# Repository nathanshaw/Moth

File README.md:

# Speculator
This repo holds all the code, schematics, and PCB layouts for all series of the Speculator bot.

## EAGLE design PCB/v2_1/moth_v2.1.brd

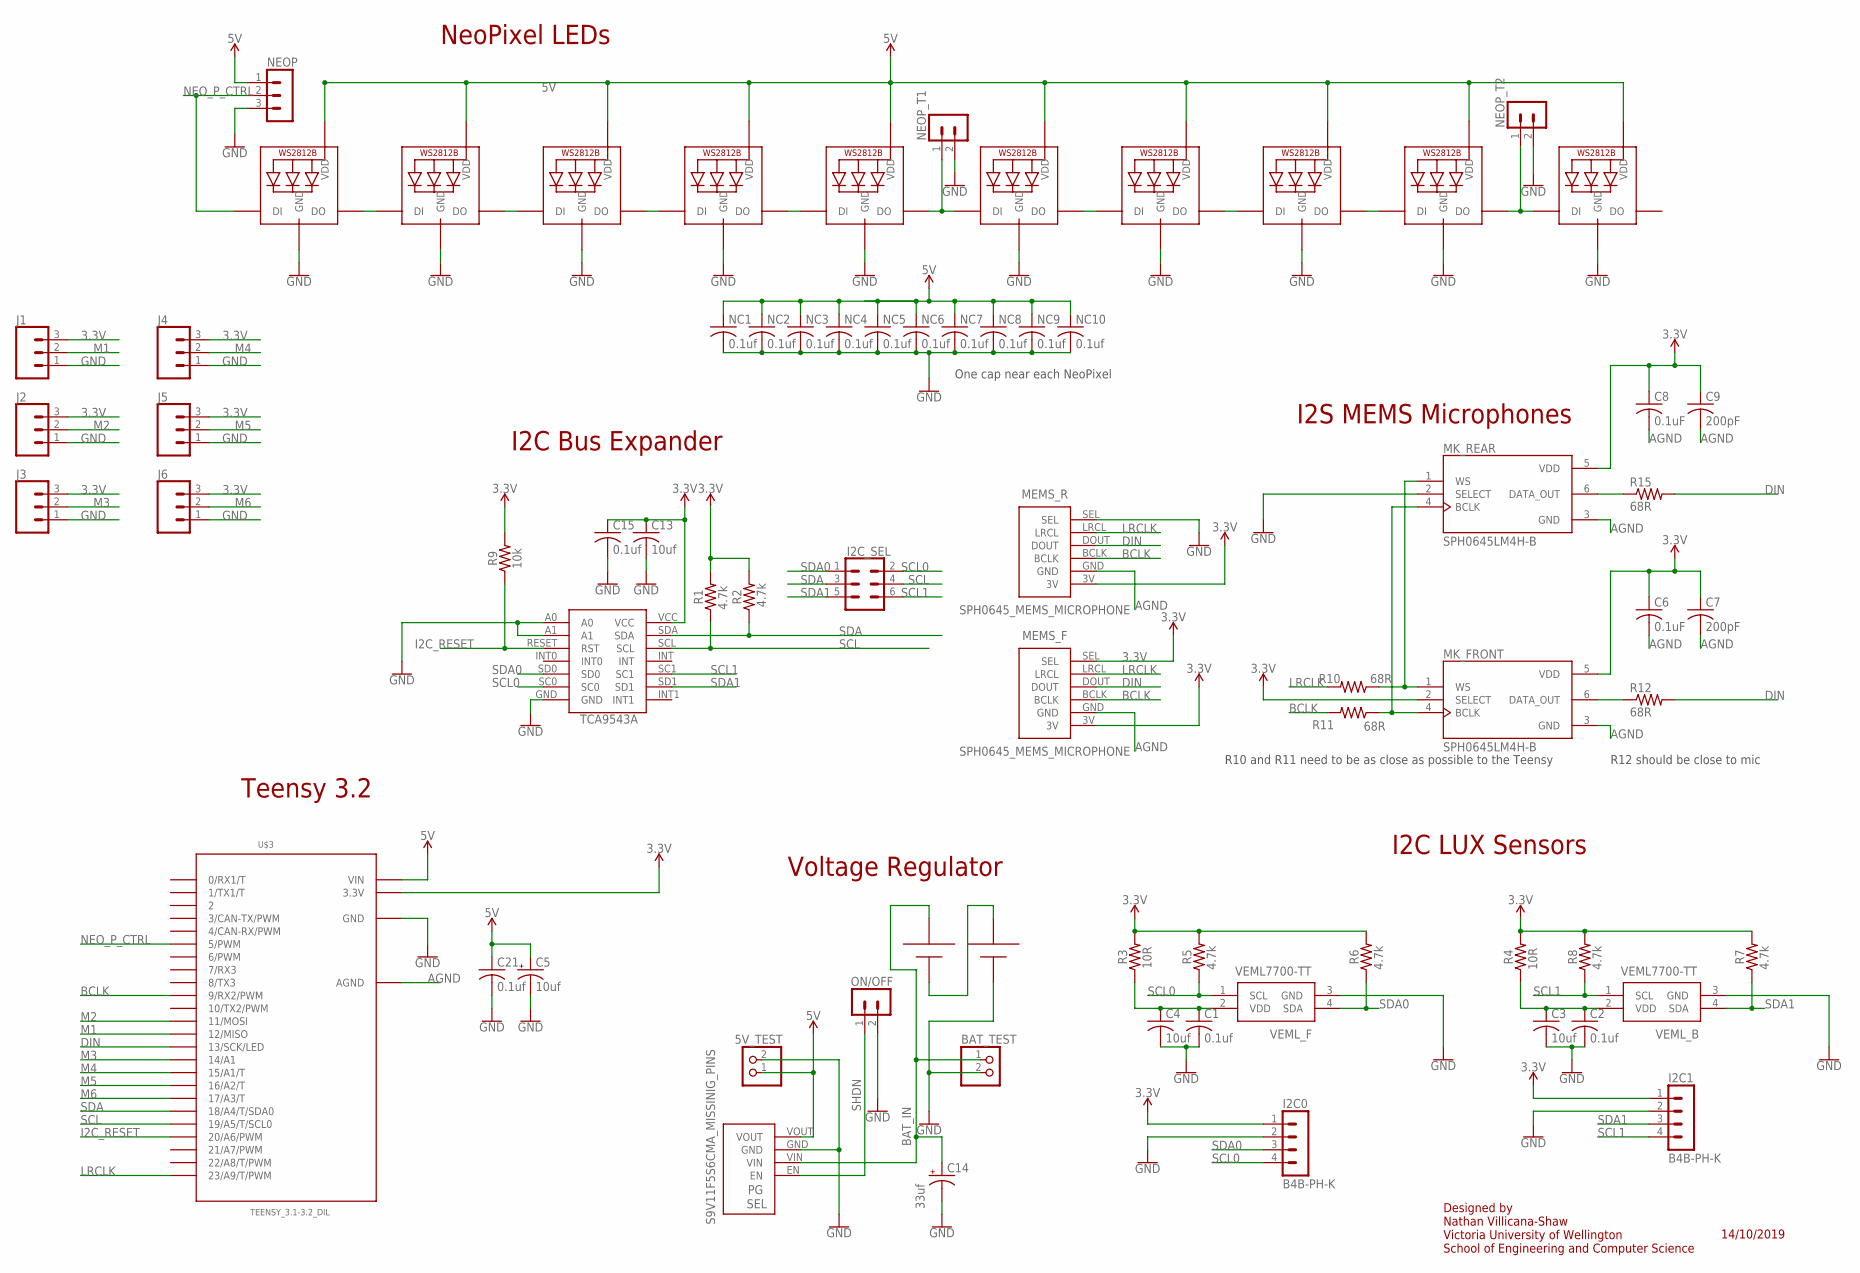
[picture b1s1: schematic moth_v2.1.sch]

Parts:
5V_TEST: PINHD-1X2; 1X02
BAT_TEST: PINHD-1X2; 1X02
C1, C2, C15, C21: 0.1uf; C1206K
C3, C4, C13: 10uf; C1206K
C5: 10uf; E2,5-6
C6, C8: 0.1uF; C1206K
C7, C9: 200pF; C1206K
C14: 33uf; E2-5
I2C0, I2C1: B4B-PH-K
I2C_SEL: FEMALE 2x3; 2X3
J1, J2, J3, J4, J5, J6: CONN_03; 1X03
MEMS_F: SPH0645_MEMS_MICROPHONE; SPH0645
MEMS_R: SPH0645_MEMS_MICROPHONE; SPH0645
MK_FRONT: SPH0645LM4H-B; MIC_SPH0645LM4H-B
MK_REAR: SPH0645LM4H-B; MIC_SPH0645LM4H-B
NC1, NC2, NC3, NC4, NC5, NC6, NC7, NC8, NC9, NC10: 0.1uf; C1206K
NEO1, NEO2, NEO3, NEO4, NEO5, NEO6, NEO7, NEO8, NEO9, NEO10: WS2812B5050; WS2812B
NEOP: B3B-PH-K
NEOP_T1, NEOP_T2: B2B-PH-K
ON/OFF: B2B-PH-K
R1, R2, R5, R6, R7, R8: 4.7k; R1206W
R3, R4: 10R; R1206W
R9: 10k; R1206W
R10, R11, R12, R15: 68R; M1206
U$1: TCA9543A; SO14
U$2: BK-18650-PC4; 18650-PC4
U$3: TEENSY_3.1-3.2_DIL; TEENSY_3.0-3.2&LC_DIL
U$6: S9V11F5S6CMA_MISSINIG_PINS; S9V11F3S5CMA_MISSING_PINS
VEML_B: VEML7700-TT; VEML7700
VEML_F: VEML7700-TT; VEML7700

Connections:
3.3V: C6.1, C7.1, C8.1, C9.1, C13.1, C15.1, I2C0.1, I2C1.1, J1.3, J2.3, J3.3, J4.3, J5.3, J6.3, MEMS_F.3V, MEMS_F.SEL, MEMS_R.3V, MK_FRONT.2 (SELECT), MK_FRONT.5 (VDD), MK_REAR.5 (VDD), R1.2, R2.2, R3.2, R4.2, R5.2, R6.2, R7.2, R8.2, R9.2, U$1.VCC, U$3.3.3V
5V: 5V_TEST.1, C5.+, C21.1, NC1.1, NC2.1, NC3.1, NC4.1, NC5.1, NC6.1, NC7.1, NC8.1, NC9.1, NC10.1, NEO1.1-VDD (VDD), NEO2.1-VDD (VDD), NEO3.1-VDD (VDD), NEO4.1-VDD (VDD), NEO5.1-VDD (VDD), NEO6.1-VDD (VDD), NEO7.1-VDD (VDD), NEO8.1-VDD (VDD), NEO9.1-VDD (VDD), NEO10.1-VDD (VDD), NEOP.1, U$3.VIN, U$6.VOUT
AGND: C6.2, C7.2, C8.2, C9.2, MEMS_F.GND, MEMS_R.GND, MK_FRONT.3 (GND), MK_REAR.3 (GND), U$3.AGND
BAT_IN: BAT_TEST.1, C14.+, U$2.+1, U$6.VIN
BCLK: MEMS_F.BCLK, MEMS_R.BCLK, R11.2, U$3.9 (9/RX2/PWM)
BCLK_P: MK_FRONT.4 (BCLK), MK_REAR.4 (BCLK), R11.1
DIN: MEMS_F.DOUT, MEMS_R.DOUT, R12.2, R15.2, U$3.13 (13/SCK/LED)
GND: 5V_TEST.2, BAT_TEST.2, C1.2, C2.2, C3.2, C4.2, C5.-, C13.2, C14.-, C15.2, C21.2, I2C0.2, I2C1.2, J1.1, J2.1, J3.1, J4.1, J5.1, J6.1, MEMS_R.SEL, MK_REAR.2 (SELECT), NC1.2, NC2.2, NC3.2, NC4.2, NC5.2, NC6.2, NC7.2, NC8.2, NC9.2, NC10.2, NEO1.3-GND (GND), NEO2.3-GND (GND), NEO3.3-GND (GND), NEO4.3-GND (GND), NEO5.3-GND (GND), NEO6.3-GND (GND), NEO7.3-GND (GND), NEO8.3-GND (GND), NEO9.3-GND (GND), NEO10.3-GND (GND), NEOP.3, NEOP_T1.2, NEOP_T2.2, ON/OFF.2, U$1.A0, U$1.A1, U$1.GND, U$2.-2, U$3.GND, U$6.GND, VEML_B.3 (GND), VEML_F.3 (GND)
I2C_RESET: R9.1, U$1.RESET (RST), U$3.20/A6 (20/A6/PWM)
LRCLK: MEMS_F.LRCL, MEMS_R.LRCL, R10.2, U$3.23/A9 (23/A9/T/PWM)
LRCLK_P: MK_FRONT.1 (WS), MK_REAR.1 (WS), R10.1
M1: J1.2, U$3.12 (12/MISO)
M2: J2.2, U$3.11 (11/MOSI)
M3: J3.2, U$3.14/A0 (14/A1)
M4: J4.2, U$3.15/A1 (15/A1/T)
M5: J5.2, U$3.16/A2 (16/A2/T)
M6: J6.2, U$3.17/A3 (17/A3/T)
unnamed: C1.1, C4.1, R3.1, VEML_F.2 (VDD)
unnamed: C2.1, C3.1, R4.1, VEML_B.2 (VDD)
unnamed: MK_FRONT.6 (DATA_OUT), R12.1
unnamed: NEO2.2-DOUT (DO), NEO3.4-DIN (DI)
unnamed: NEO5.2-DOUT (DO), NEO6.4-DIN (DI), NEOP_T1.1
unnamed: NEO9.2-DOUT (DO), NEO10.4-DIN (DI), NEOP_T2.1
unnamed: NEO4.2-DOUT (DO), NEO5.4-DIN (DI)
unnamed: NEO3.2-DOUT (DO), NEO4.4-DIN (DI)
unnamed: NEO7.2-DOUT (DO), NEO8.4-DIN (DI)
unnamed: NEO8.2-DOUT (DO), NEO9.4-DIN (DI)
unnamed: MK_REAR.6 (DATA_OUT), R15.1
unnamed: U$2.+2, U$2.-1
unnamed: NEO6.2-DOUT (DO), NEO7.4-DIN (DI)
NEO_P1: NEO1.2-DOUT (DO), NEO2.4-DIN (DI)
NEO_P_CTRL: NEO1.4-DIN (DI), NEOP.2, U$3.5 (5/PWM)
SCL: I2C_SEL.4, R1.1, U$1.SCL, U$3.19/A5 (19/A5/T/SCL0)
SCL0: I2C0.4, I2C_SEL.2, R5.1, U$1.SC0, VEML_F.1 (SCL)
SCL1: I2C1.4, I2C_SEL.6, R8.1, U$1.SC1, VEML_B.1 (SCL)
SDA: I2C_SEL.3, R2.1, U$1.SDA, U$3.18/A4 (18/A4/T/SDA0)
SDA0: I2C0.3, I2C_SEL.1, R6.1, U$1.SD0, VEML_F.4 (SDA)
SDA1: I2C1.3, I2C_SEL.5, R7.1, U$1.SD1, VEML_B.4 (SDA)
SHDN: ON/OFF.1, U$6.EN

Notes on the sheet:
I2S MEMS Microphones
Voltage Regulator
I2C LUX Sensors
I2C Bus Expander
NeoPixel LEDs
10k
4.7k
One cap near each NeoPixel
R10 and R11 need to be as close as possible to the Teensy
R12 should be close to mic
10R
Teensy 3.2
Designed by Nathan Villicana-Shaw Victoria University of Wellington School of Engineering and Computer Science
14/10/2019

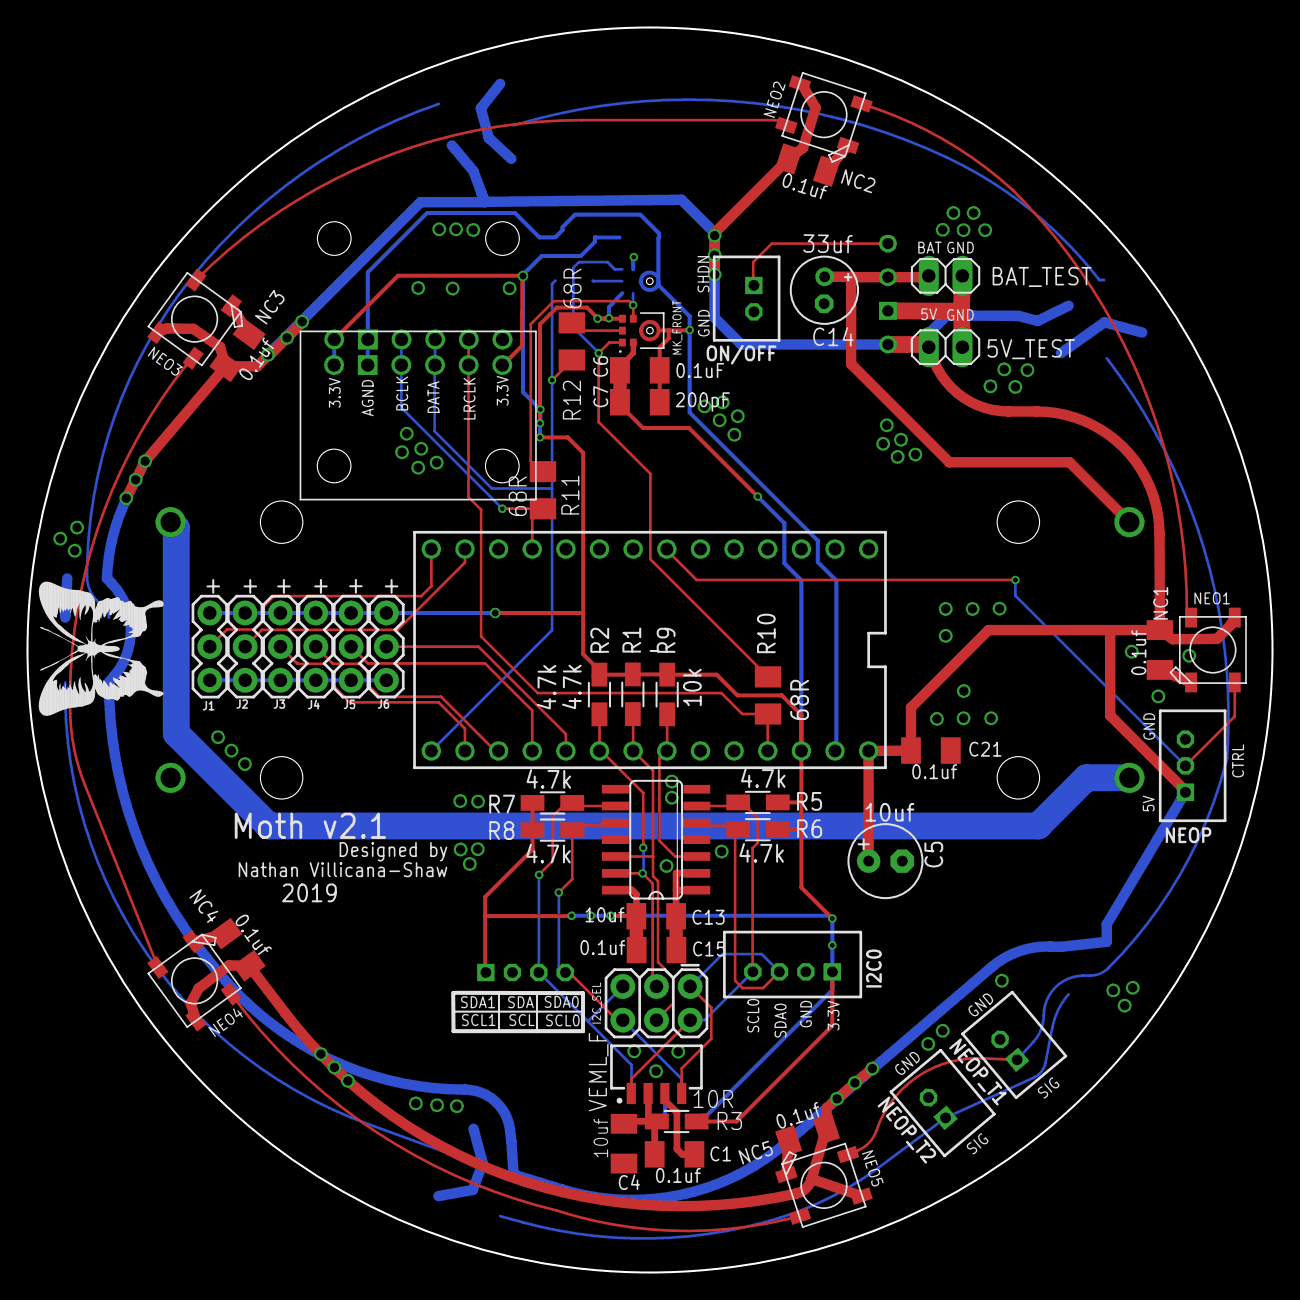
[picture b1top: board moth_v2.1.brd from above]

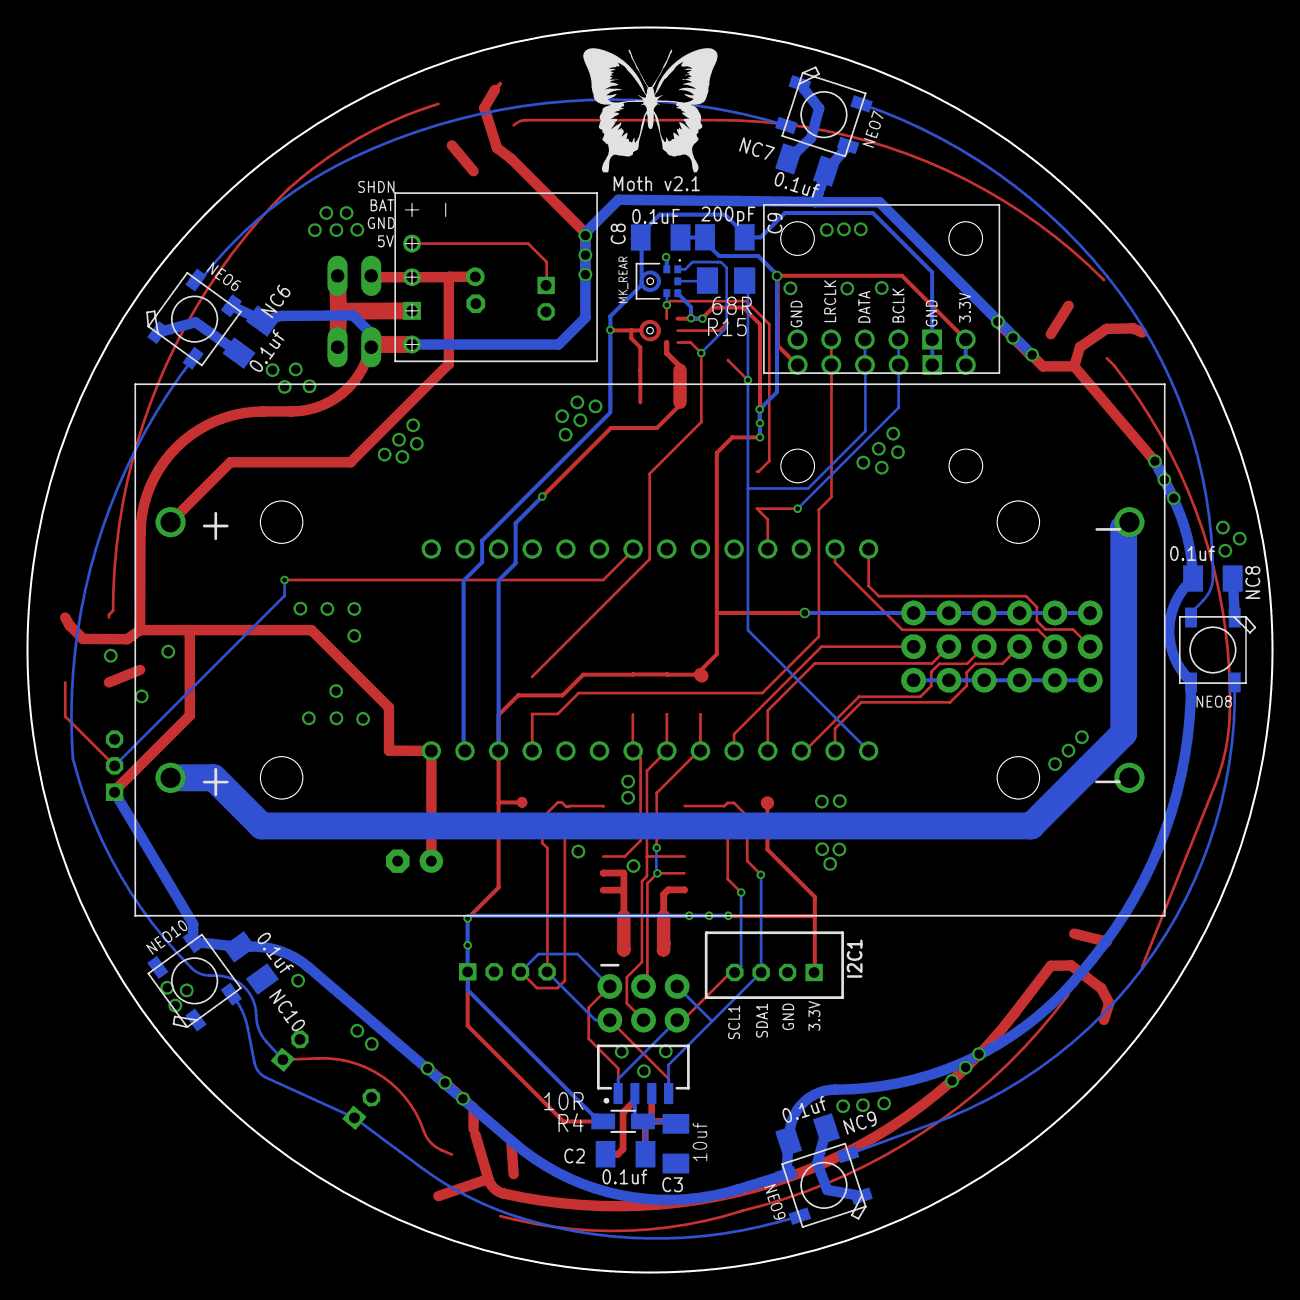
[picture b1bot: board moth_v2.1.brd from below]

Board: 2 copper layers, 94.0 x 94.0 mm, 71 parts (22 on the bottom side), 39 nets.

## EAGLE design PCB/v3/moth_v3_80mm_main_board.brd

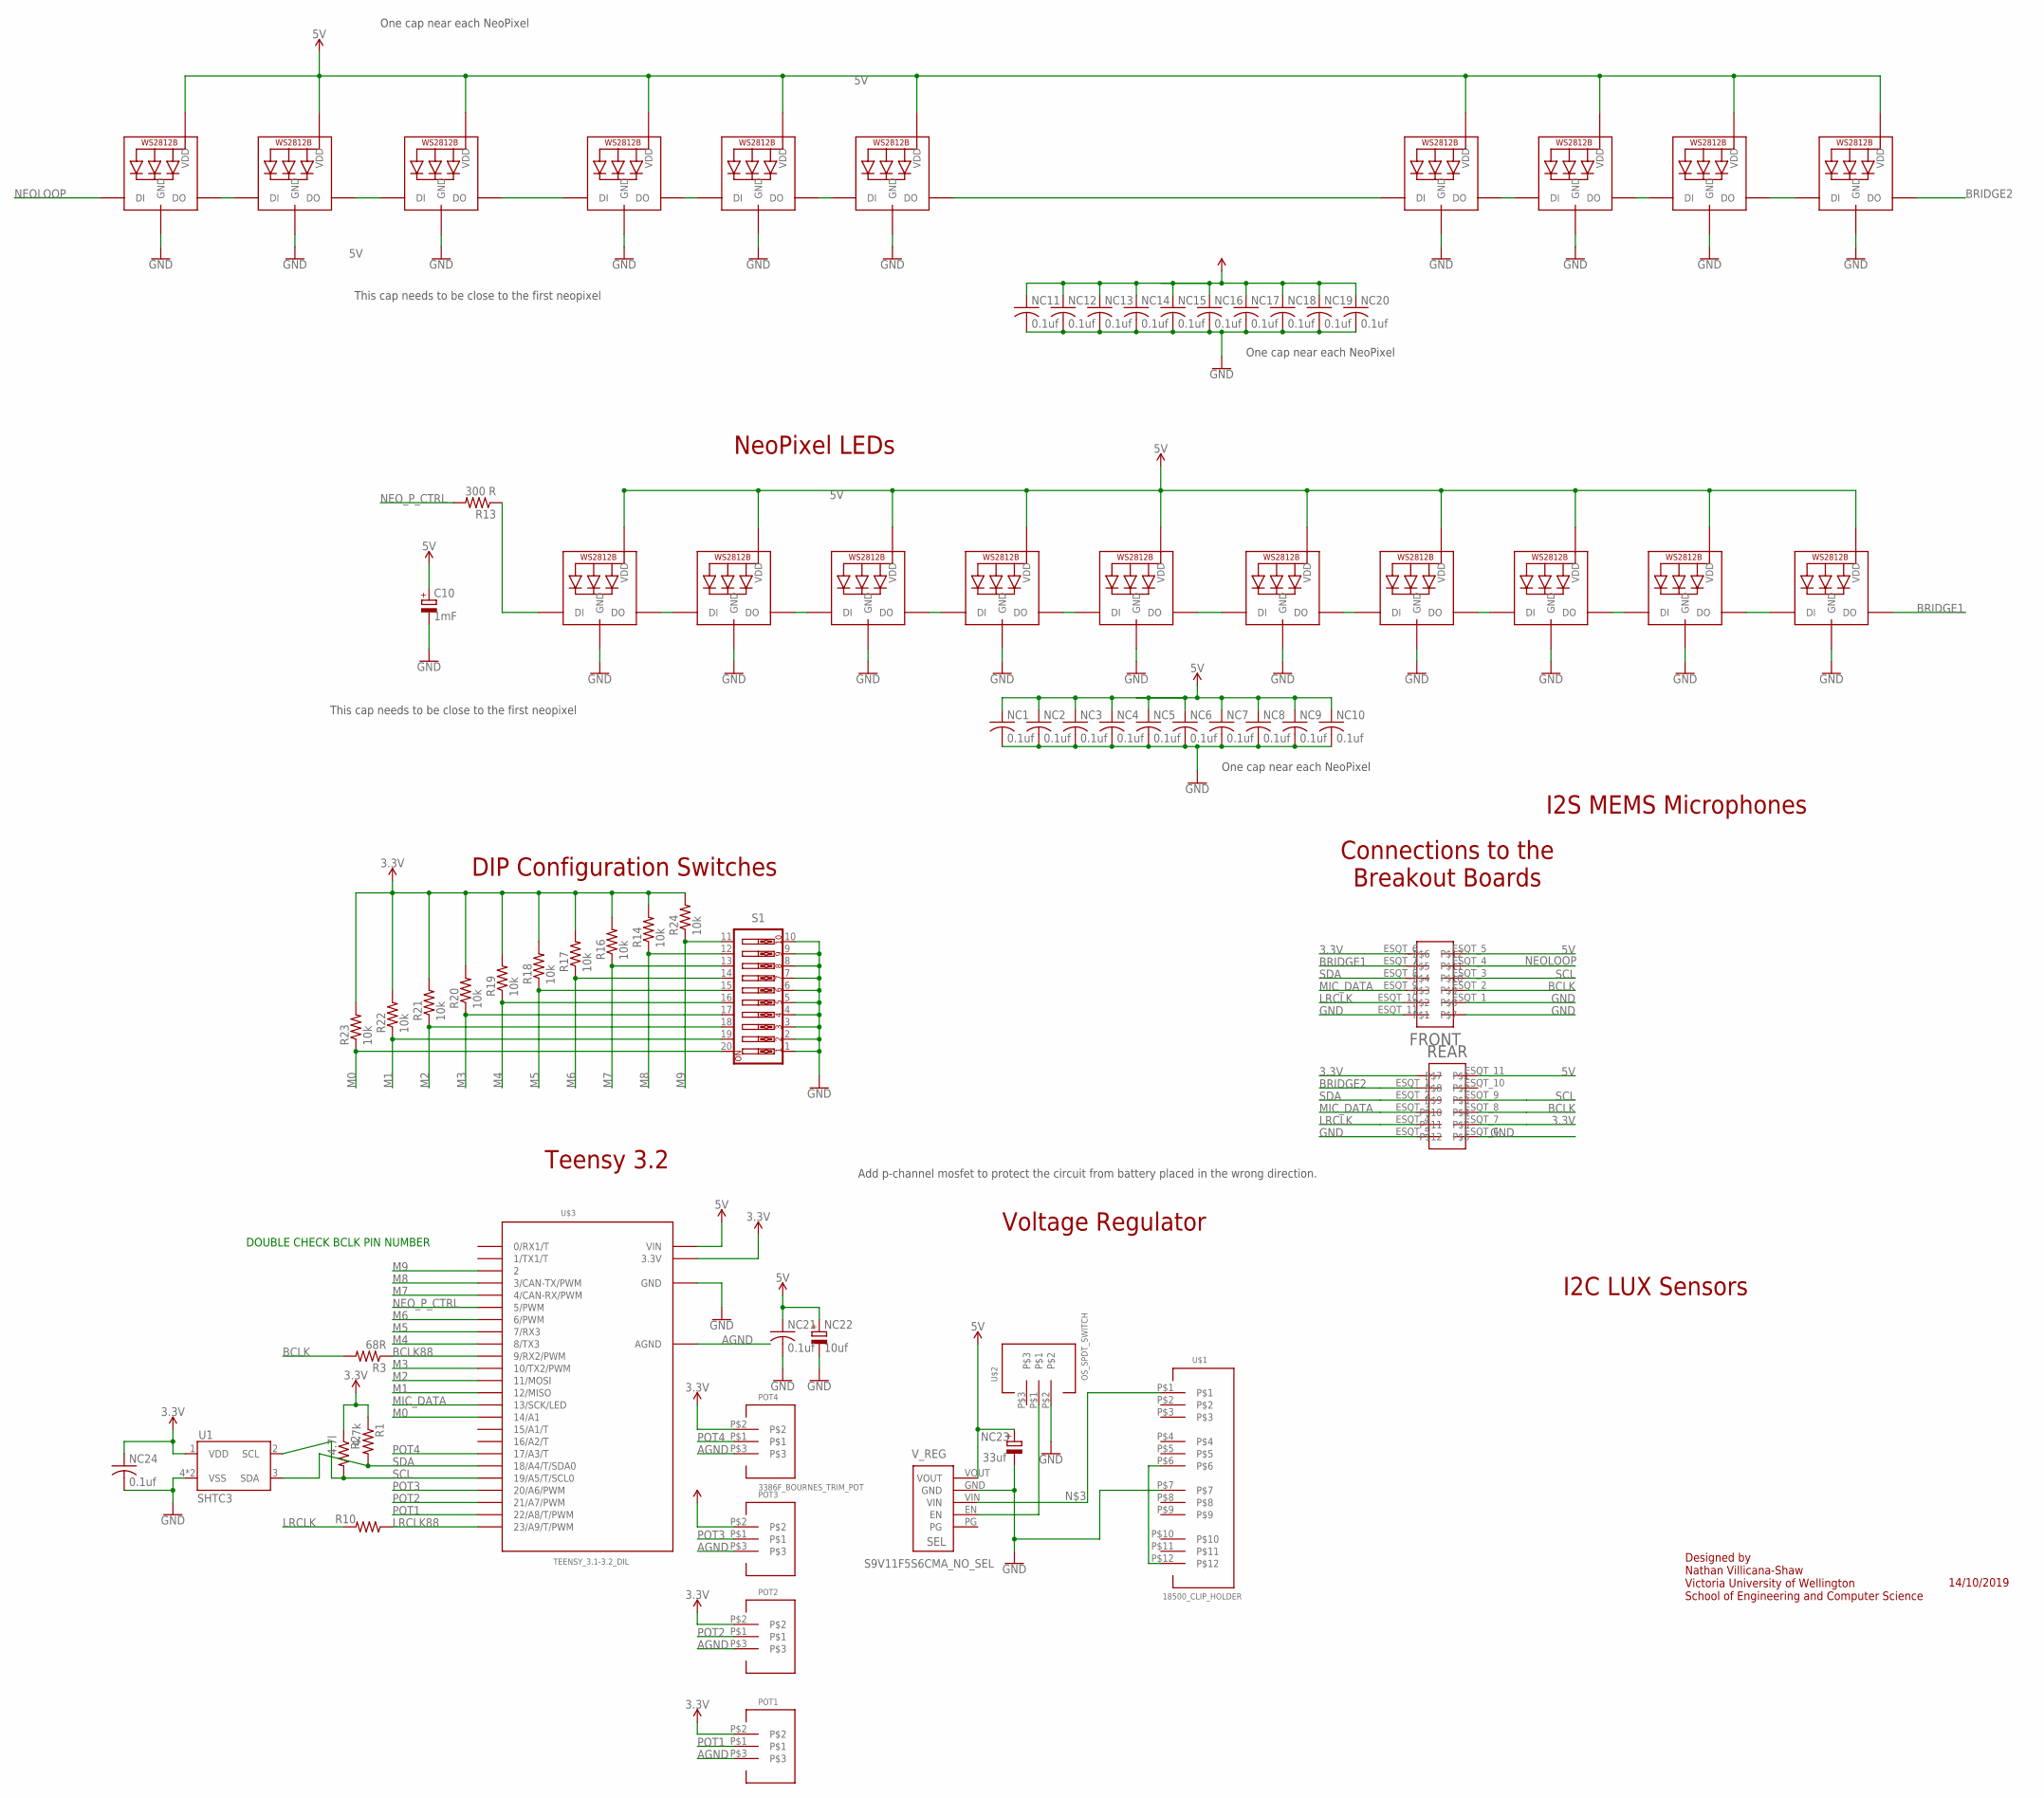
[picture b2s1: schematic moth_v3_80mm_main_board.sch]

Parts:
C10: 1mF; 153CLV-1010
FRONT: SAMTEC_ESQT_2X6_THROUGH_HOLE
NC1, NC2, NC3, NC4, NC5, NC6, NC7, NC8, NC9, NC10, NC11, NC12, NC13, NC14, NC15, NC16, NC17, NC18, NC19, NC20, NC21, NC24: 0.1uf; C0805K
NC22: 10uf; E2,5-7
NC23: 33uf; E2,5-7
NEO1, NEO2, NEO3, NEO4, NEO5, NEO6, NEO7, NEO8, NEO9, NEO10, NEO11, NEO12, NEO13, NEO14, NEO15, NEO16, NEO17, NEO18, NEO19, NEO20: WS2812B5050; WS2812B
POT1, POT2, POT3, POT4: 3386F_BOURNES_TRIM_POT; 3386_BOURNS_TRIM_POT
R1: 4.7k; R0805
R2: 4.7l; R0805
R3, R10: 68R; R0805
R13: 300 R; R0805
R14, R16, R17, R18, R19, R20, R21, R22, R24: 10k; R0805
R23: 10k; M0805
REAR: SAMTEC_ESQT_2X6_THROUGH_HOLE
S1: SW_DIP-10; EDG-10
U1: SHTC3
U$1: 18500_CLIP_HOLDER; 3PINBATTERY_CLIP
U$2: OS_SPDT_SWITCH; OS_SPDT_SLIDE_SWITCH
U$3: TEENSY_3.1-3.2_DIL; TEENSY_3.0-3.2&LC_DIL
V_REG: S9V11F5S6CMA_NO_SEL; S9V11F3S5CMA_NO_SEL

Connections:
3.3V: FRONT.ESQT_6, NC24.1, POT1.P$2, POT2.P$2, POT3.P$2, POT4.P$2, R1.1, R2.1, R14.2, R16.2, R17.2, R18.2, R19.2, R20.2, R21.2, R22.2, R23.2, R24.2, REAR.ESQT_0, REAR.ESQT_7, U1.1 (VDD), U$3.3.3V
5V: C10.+, FRONT.ESQT_5, NC1.1, NC2.1, NC3.1, NC4.1, NC5.1, NC6.1, NC7.1, NC8.1, NC9.1, NC10.1, NC11.1, NC12.1, NC13.1, NC14.1, NC15.1, NC16.1, NC17.1, NC18.1, NC19.1, NC20.1, NC21.1, NC22.+, NC23.+, NEO1.1-VDD (VDD), NEO2.1-VDD (VDD), NEO3.1-VDD (VDD), NEO4.1-VDD (VDD), NEO5.1-VDD (VDD), NEO6.1-VDD (VDD), NEO7.1-VDD (VDD), NEO8.1-VDD (VDD), NEO9.1-VDD (VDD), NEO10.1-VDD (VDD), NEO11.1-VDD (VDD), NEO12.1-VDD (VDD), NEO13.1-VDD (VDD), NEO14.1-VDD (VDD), NEO15.1-VDD (VDD), NEO16.1-VDD (VDD), NEO17.1-VDD (VDD), NEO18.1-VDD (VDD), NEO19.1-VDD (VDD), NEO20.1-VDD (VDD), REAR.ESQT_11, U$3.VIN, V_REG.VOUT
AGND: POT1.P$3, POT2.P$3, POT3.P$3, POT4.P$3, U$3.AGND
BCLK: FRONT.ESQT_2, R3.2, REAR.ESQT_8
BCLK88: R3.1, U$3.9 (9/RX2/PWM)
BRIDGE1: FRONT.ESQT_7, NEO10.2-DOUT (DO)
BRIDGE2: NEO20.2-DOUT (DO), REAR.ESQT_1
GND: C10.-, FRONT.ESQT_0, FRONT.ESQT_1, FRONT.ESQT_11, NC1.2, NC2.2, NC3.2, NC4.2, NC5.2, NC6.2, NC7.2, NC8.2, NC9.2, NC10.2, NC11.2, NC12.2, NC13.2, NC14.2, NC15.2, NC16.2, NC17.2, NC18.2, NC19.2, NC20.2, NC21.2, NC22.-, NC23.-, NC24.2, NEO1.3-GND (GND), NEO2.3-GND (GND), NEO3.3-GND (GND), NEO4.3-GND (GND), NEO5.3-GND (GND), NEO6.3-GND (GND), NEO7.3-GND (GND), NEO8.3-GND (GND), NEO9.3-GND (GND), NEO10.3-GND (GND), NEO11.3-GND (GND), NEO12.3-GND (GND), NEO13.3-GND (GND), NEO14.3-GND (GND), NEO15.3-GND (GND), NEO16.3-GND (GND), NEO17.3-GND (GND), NEO18.3-GND (GND), NEO19.3-GND (GND), NEO20.3-GND (GND), REAR.ESQT_5, REAR.ESQT_6, S1.1, S1.2, S1.3, S1.4, S1.5, S1.6, S1.7, S1.8, S1.9, S1.10, U1.4 (VSS), U1.5 (VSS), U$1.P$7, U$2.P$2, U$3.GND, V_REG.GND
LRCLK: FRONT.ESQT_10, R10.2, REAR.ESQT_4
LRCLK88: R10.1, U$3.23/A9 (23/A9/T/PWM)
M0: R23.1, S1.20, U$3.14/A0 (14/A1)
M1: R22.1, S1.19, U$3.12 (12/MISO)
M2: R21.1, S1.18, U$3.11 (11/MOSI)
M3: R20.1, S1.17, U$3.10 (10/TX2/PWM)
M4: R19.1, S1.16, U$3.8 (8/TX3)
M5: R18.1, S1.15, U$3.7 (7/RX3)
M6: R17.1, S1.14, U$3.6 (6/PWM)
M7: R16.1, S1.13, U$3.4 (4/CAN-RX/PWM)
M8: R14.1, S1.12, U$3.3 (3/CAN-TX/PWM)
M9: R24.1, S1.11, U$3.2
MIC_DATA: FRONT.ESQT_9, REAR.ESQT_3, U$3.13 (13/SCK/LED)
unnamed: U$1.P$6, U$1.P$12
unnamed: U$1.P$1, V_REG.VIN
unnamed: NEO2.2-DOUT (DO), NEO3.4-DIN (DI)
unnamed: NEO5.2-DOUT (DO), NEO6.4-DIN (DI)
unnamed: NEO9.2-DOUT (DO), NEO10.4-DIN (DI)
unnamed: NEO11.2-DOUT (DO), NEO12.4-DIN (DI)
unnamed: NEO4.2-DOUT (DO), NEO5.4-DIN (DI)
unnamed: NEO15.2-DOUT (DO), NEO16.4-DIN (DI)
unnamed: NEO3.2-DOUT (DO), NEO4.4-DIN (DI)
unnamed: NEO7.2-DOUT (DO), NEO8.4-DIN (DI)
unnamed: NEO8.2-DOUT (DO), NEO9.4-DIN (DI)
unnamed: NEO18.2-DOUT (DO), NEO19.4-DIN (DI)
unnamed: NEO13.2-DOUT (DO), NEO14.4-DIN (DI)
unnamed: NEO16.2-DOUT (DO), NEO17.4-DIN (DI)
unnamed: NEO12.2-DOUT (DO), NEO13.4-DIN (DI)
unnamed: NEO19.2-DOUT (DO), NEO20.4-DIN (DI)
unnamed: NEO6.2-DOUT (DO), NEO7.4-DIN (DI)
unnamed: NEO17.2-DOUT (DO), NEO18.4-DIN (DI)
NEOLOOP: FRONT.ESQT_4, NEO11.4-DIN (DI)
NEO_P1: NEO1.2-DOUT (DO), NEO2.4-DIN (DI)
NEO_P2: NEO14.2-DOUT (DO), NEO15.4-DIN (DI)
NEO_P_CTRL: R13.2, U$3.5 (5/PWM)
NEO_P_CTRL_INT: NEO1.4-DIN (DI), R13.1
POT1: POT1.P$1, U$3.22/A8 (22/A8/T/PWM)
POT2: POT2.P$1, U$3.21/A7 (21/A7/PWM)
POT3: POT3.P$1, U$3.20/A6 (20/A6/PWM)
POT4: POT4.P$1, U$3.17/A3 (17/A3/T)
SCL: FRONT.ESQT_3, R2.2, REAR.ESQT_9, U1.2 (SCL), U$3.19/A5 (19/A5/T/SCL0)
SDA: FRONT.ESQT_8, R1.2, REAR.ESQT_2, U1.3 (SDA), U$3.18/A4 (18/A4/T/SDA0)
SHDN: U$2.P$1, V_REG.EN

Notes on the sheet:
I2S MEMS Microphones
Voltage Regulator
I2C LUX Sensors
NeoPixel LEDs
One cap near each NeoPixel
Teensy 3.2
Designed by Nathan Villicana-Shaw Victoria University of Wellington School of Engineering and Computer Science
14/10/2019
DIP Configuration Switches
This cap needs to be close to the first neopixel
Add p-channel mosfet to protect the circuit from battery placed in the wrong direction.
Connections to the Breakout Boards
DOUBLE CHECK BCLK PIN NUMBER

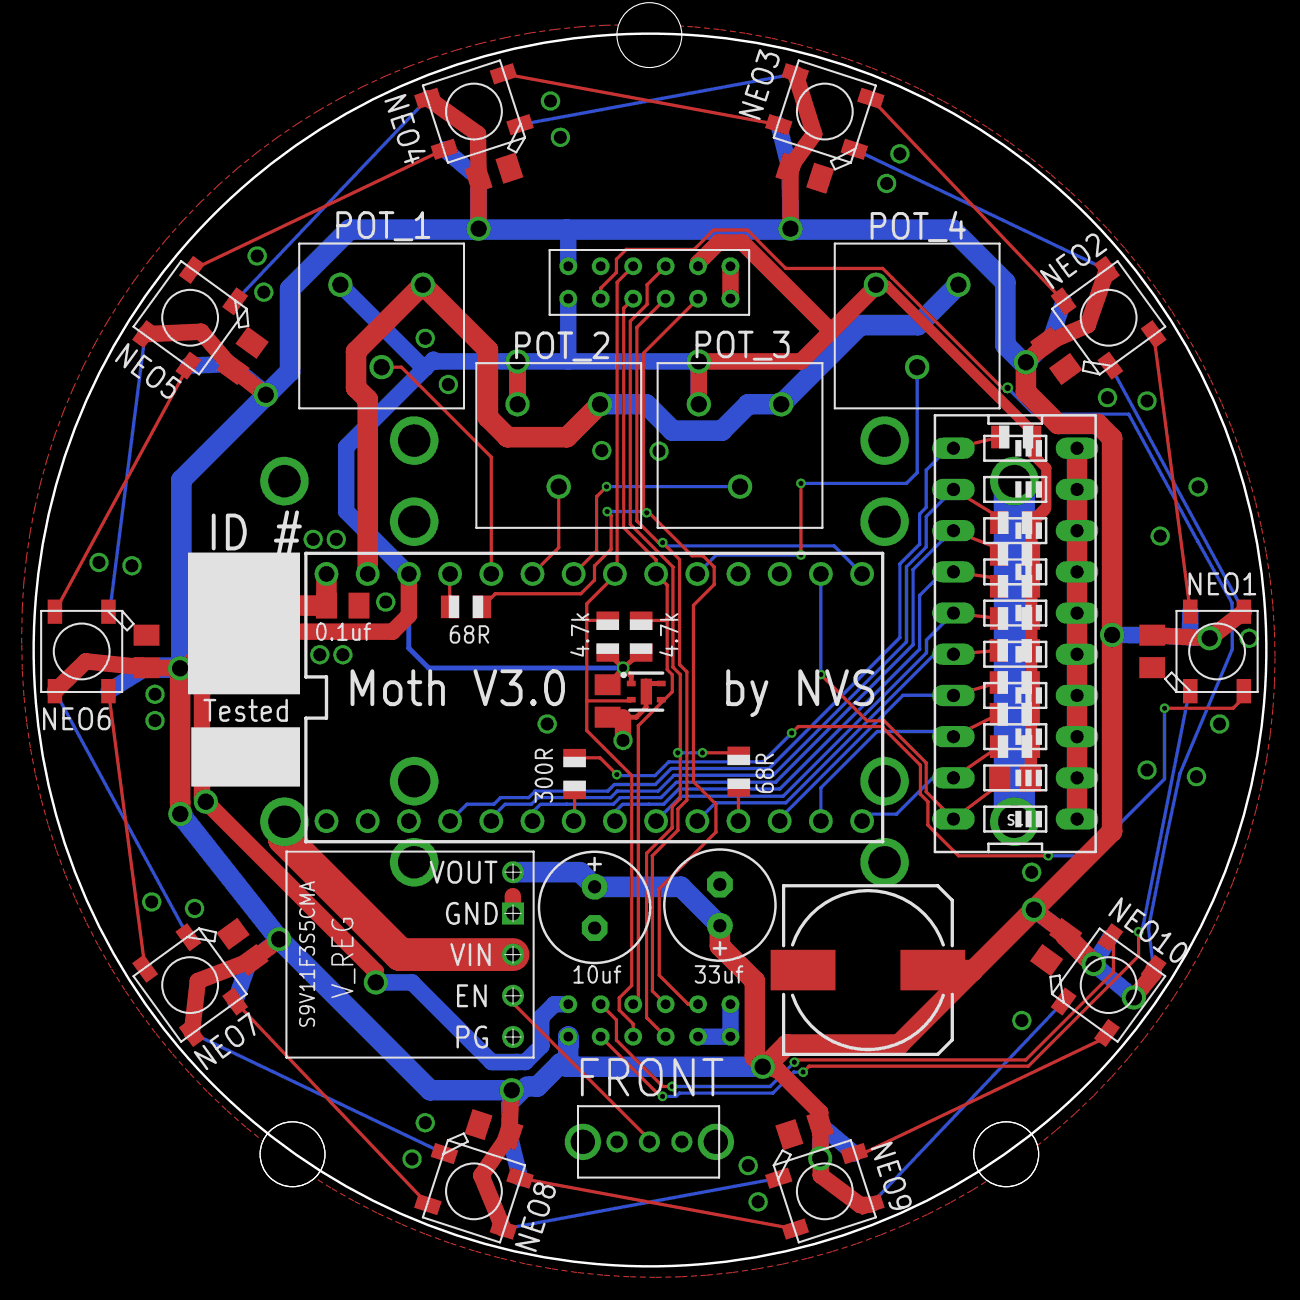
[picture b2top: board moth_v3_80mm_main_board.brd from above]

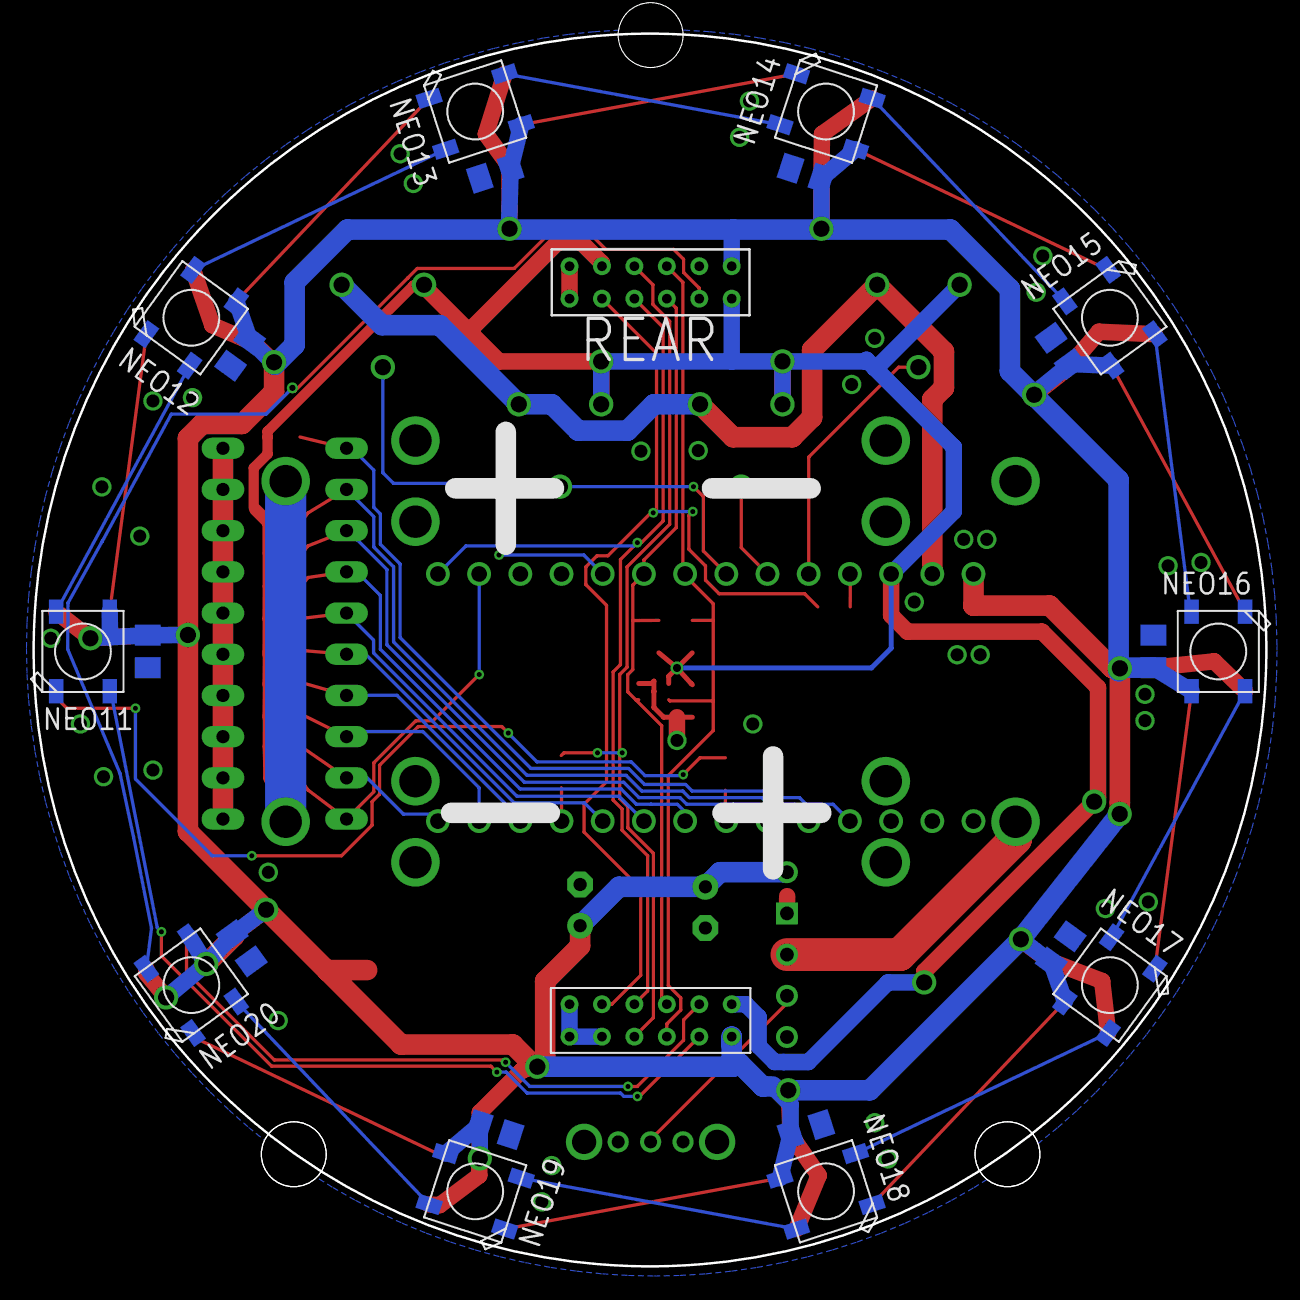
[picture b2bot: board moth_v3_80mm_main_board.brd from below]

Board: 2 copper layers, 76.0 x 76.0 mm, 72 parts (22 on the bottom side), 51 nets.

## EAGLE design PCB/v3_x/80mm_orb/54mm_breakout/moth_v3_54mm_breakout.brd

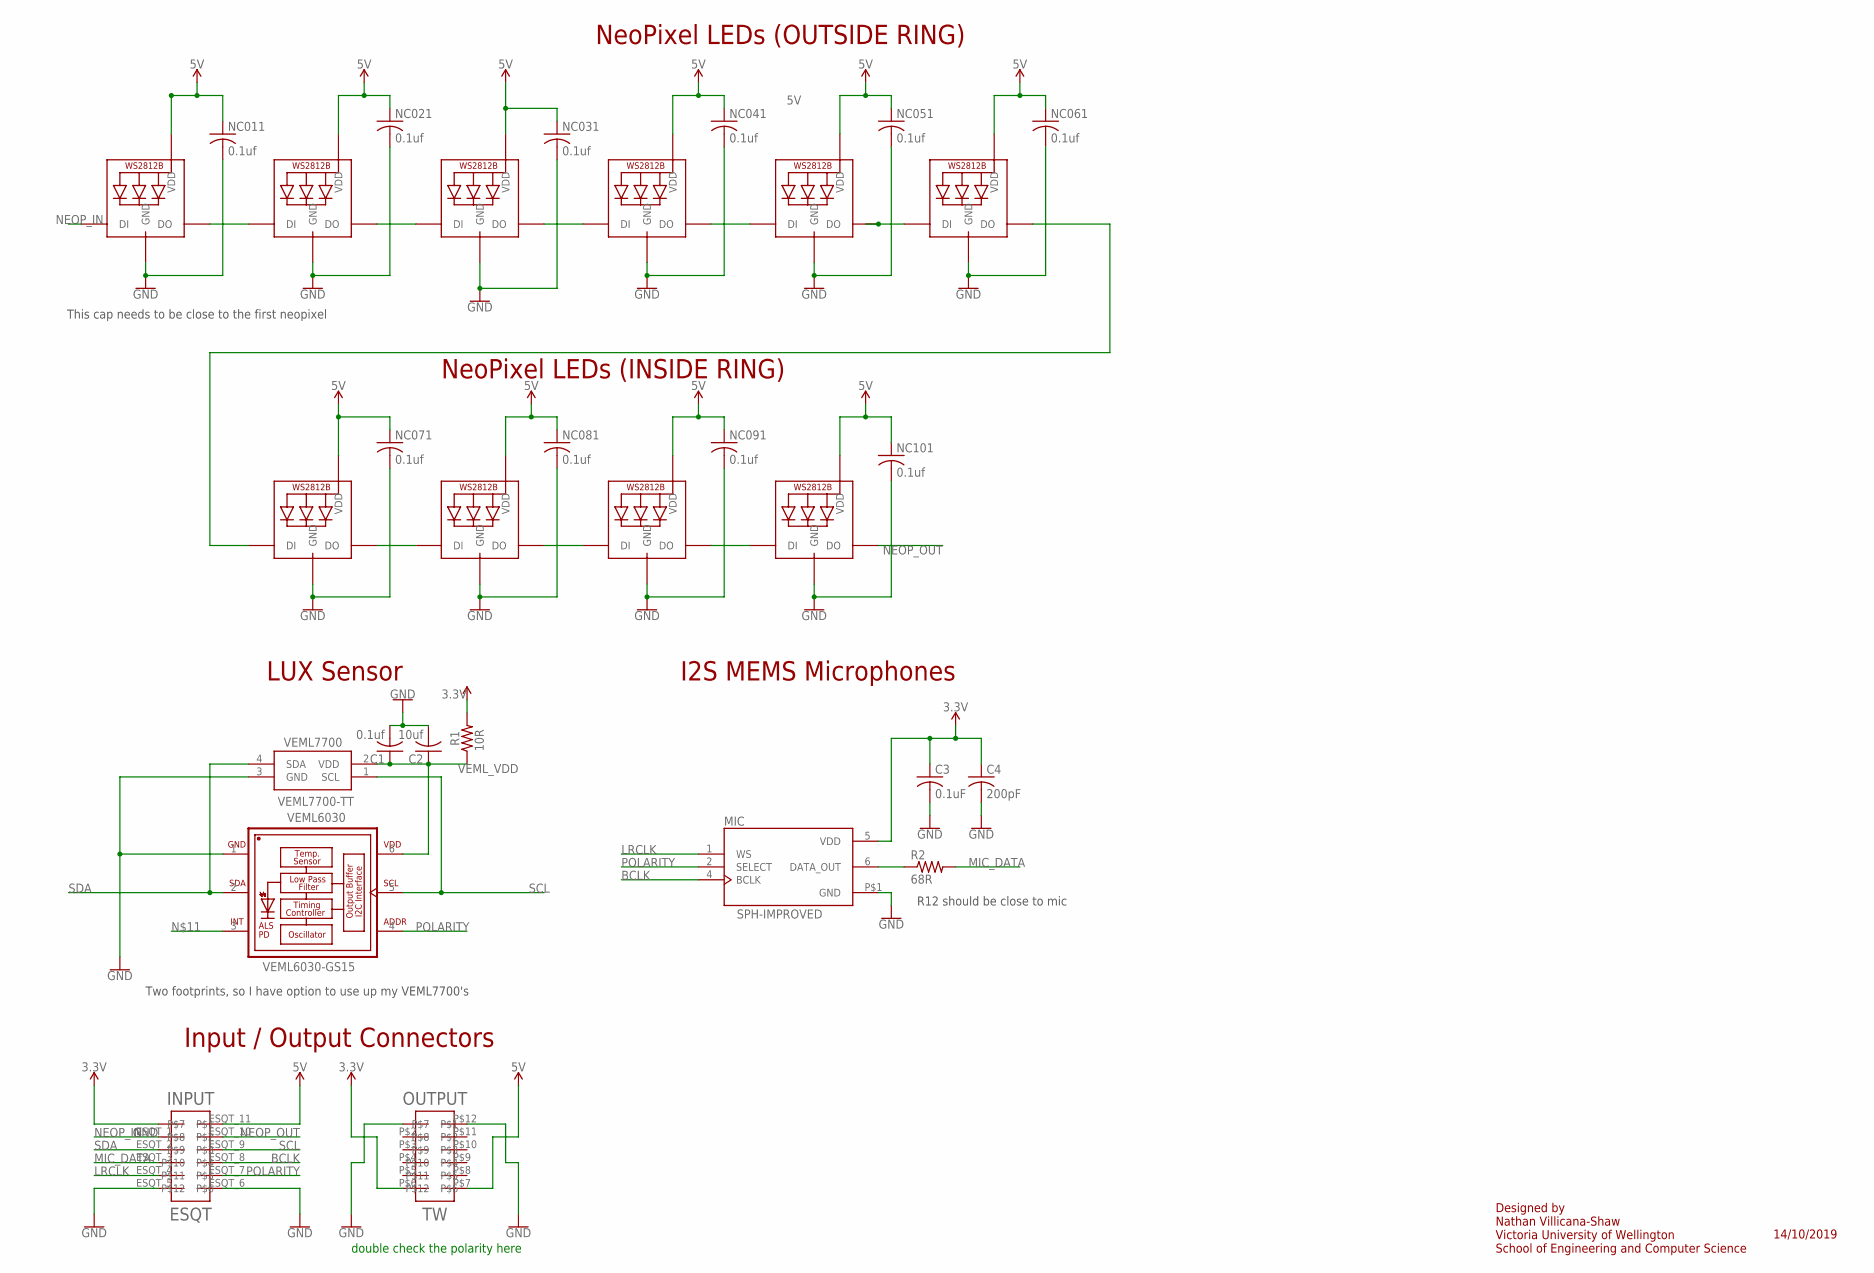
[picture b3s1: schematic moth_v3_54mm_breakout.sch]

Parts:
C1: 0.1uf; C0805
C2: 10uf; C0805
C3: 0.1uF; C0805
C4: 200pF; C0805
INPUT: ESQT; SAMTEC_ESQT_2X6_THROUGH_HOLE
MIC: SPH-IMPROVED; MIC_SPH0645LM4H-B_LARGER_RING
NC011, NC021, NC031, NC041, NC051, NC061, NC071, NC081, NC091, NC101: 0.1uf; C0805K
NEO1, NEO2, NEO3, NEO4, NEO5, NEO6, NEO07, NEO08, NEO9, NEO10: WS2812B5050; WS2812B
OUTPUT: TW; SAMTEC_TW_2X6
R1: 10R; R0805
R2: 68R; M0805
VEML6030: VEML6030-GS15; VISHAY_VEML6030_2X2X0.87
VEML7700: VEML7700-TT; VEML7700

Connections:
3.3V: C3.1, C4.1, INPUT.ESQT_0, MIC.5 (VDD), OUTPUT.P$6, R1.2
5V: INPUT.ESQT_11, NC011.1, NC021.1, NC031.1, NC041.1, NC051.1, NC061.1, NC071.1, NC081.1, NC091.1, NC101.1, NEO1.1-VDD (VDD), NEO2.1-VDD (VDD), NEO3.1-VDD (VDD), NEO4.1-VDD (VDD), NEO5.1-VDD (VDD), NEO6.1-VDD (VDD), NEO07.1-VDD (VDD), NEO08.1-VDD (VDD), NEO9.1-VDD (VDD), NEO10.1-VDD (VDD), OUTPUT.P$7
1232135: NEO08.2-DOUT (DO), NEO9.4-DIN (DI)
BCLK: INPUT.ESQT_8, MIC.4 (BCLK)
GND: C1.2, C2.2, C3.2, C4.2, INPUT.ESQT_5, INPUT.ESQT_6, MIC.P$1 (GND), NC011.2, NC021.2, NC031.2, NC041.2, NC051.2, NC061.2, NC071.2, NC081.2, NC091.2, NC101.2, NEO1.3-GND (GND), NEO2.3-GND (GND), NEO3.3-GND (GND), NEO4.3-GND (GND), NEO5.3-GND (GND), NEO6.3-GND (GND), NEO07.3-GND (GND), NEO08.3-GND (GND), NEO9.3-GND (GND), NEO10.3-GND (GND), OUTPUT.P$1, OUTPUT.P$12, VEML6030.1 (GND), VEML7700.3 (GND)
LRCLK: INPUT.ESQT_4, MIC.1 (WS)
MIC_DATA: INPUT.ESQT_3, R2.2
unnamed: NEO3.2-DOUT (DO), NEO4.4-DIN (DI)
unnamed: NEO4.2-DOUT (DO), NEO5.4-DIN (DI)
unnamed: NEO9.2-DOUT (DO), NEO10.4-DIN (DI)
unnamed: NEO07.2-DOUT (DO), NEO08.4-DIN (DI)
unnamed: NEO6.2-DOUT (DO), NEO07.4-DIN (DI)
unnamed: NEO5.2-DOUT (DO), NEO6.4-DIN (DI)
unnamed: NEO1.2-DOUT (DO), NEO2.4-DIN (DI)
unnamed: MIC.6 (DATA_OUT), R2.1
unnamed: NEO2.2-DOUT (DO), NEO3.4-DIN (DI)
NEOP_IN: INPUT.ESQT_1, NEO1.4-DIN (DI)
NEOP_OUT: INPUT.ESQT_10, NEO10.2-DOUT (DO)
POLARITY: INPUT.ESQT_7, MIC.2 (SELECT), VEML6030.4 (ADDR)
SCL: INPUT.ESQT_9, VEML6030.5 (SCL), VEML7700.1 (SCL)
SDA: INPUT.ESQT_2, VEML6030.2 (SDA), VEML7700.4 (SDA)
VEML_VDD: C1.1, C2.1, R1.1, VEML6030.6 (VDD), VEML7700.2 (VDD)

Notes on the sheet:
I2S MEMS Microphones
LUX Sensor
NeoPixel LEDs (OUTSIDE RING)
R12 should be close to mic
10R
Designed by Nathan Villicana-Shaw Victoria University of Wellington School of Engineering and Computer Science
14/10/2019
This cap needs to be close to the first neopixel
double check the polarity here
NeoPixel LEDs (INSIDE RING)
Input / Output Connectors
Two footprints, so I have option to use up my VEML7700's

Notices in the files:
parts and their libraries:
SparkFun-Capacitors: Licensing: Creative Commons ShareAlike 4.0 International - https://creativecommons.org/licenses/by-sa/4.0
con-jst-ph: Copyright (C) 2016, Bob Starr
